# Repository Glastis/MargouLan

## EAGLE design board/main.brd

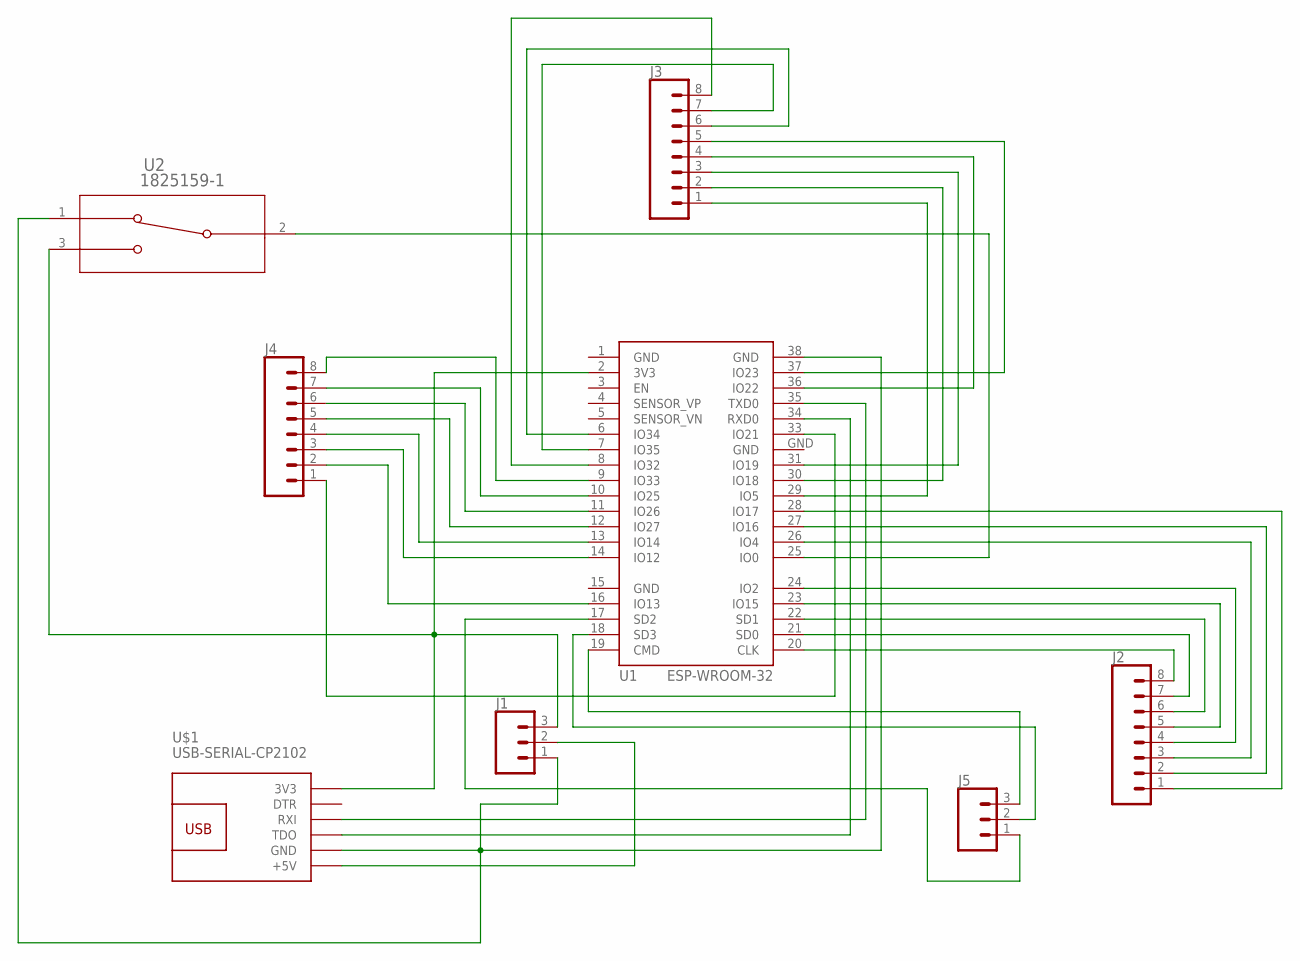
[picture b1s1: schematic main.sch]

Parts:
J1, J5: CONN_03; 1X03
J2, J3, J4: CONN_08"; 1X08
U1: ESP-WROOM-32
U2: 1825159-1; SW3-SLIDE-2POL_P98
U$1: USB-SERIAL-CP2102

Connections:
GND: U1.1 (GND), U1.15 (GND), U1.GND
unnamed: J1.3, U1.2 (3V3), U2.3 (2), U$1.1 (3V3)
unnamed: J1.1, U1.38 (GND), U2.1, U$1.5 (GND)
unnamed: U1.35 (TXD0), U$1.3 (RXI)
unnamed: U1.34 (RXD0), U$1.4 (TDO)
unnamed: U1.25 (IO0), U2.2 (3)
unnamed: J1.2, U$1.6 (+5V)
unnamed: J2.8, U1.20 (CLK)
unnamed: J2.7, U1.21 (SD0)
unnamed: J2.6, U1.22 (SD1)
unnamed: J2.5, U1.23 (IO15)
unnamed: J2.4, U1.24 (IO2)
unnamed: J2.3, U1.26 (IO4)
unnamed: J2.2, U1.27 (IO16)
unnamed: J2.1, U1.28 (IO17)
unnamed: J3.1, U1.29 (IO5)
unnamed: J3.2, U1.30 (IO18)
unnamed: J3.3, U1.31 (IO19)
unnamed: J3.4, U1.36 (IO22)
unnamed: J3.5, U1.37 (IO23)
unnamed: J3.6, U1.6 (IO34)
unnamed: J3.7, U1.7 (IO35)
unnamed: J3.8, U1.8 (IO32)
unnamed: J4.8, U1.9 (IO33)
unnamed: J4.7, U1.10 (IO25)
unnamed: J4.6, U1.11 (IO26)
unnamed: J4.5, U1.12 (IO27)
unnamed: J4.4, U1.13 (IO14)
unnamed: J4.3, U1.14 (IO12)
unnamed: J4.2, U1.16 (IO13)
unnamed: J4.1, U1.33 (IO21)
unnamed: J5.3, U1.19 (CMD)
unnamed: J5.2, U1.18 (SD3)
unnamed: J5.1, U1.17 (SD2)

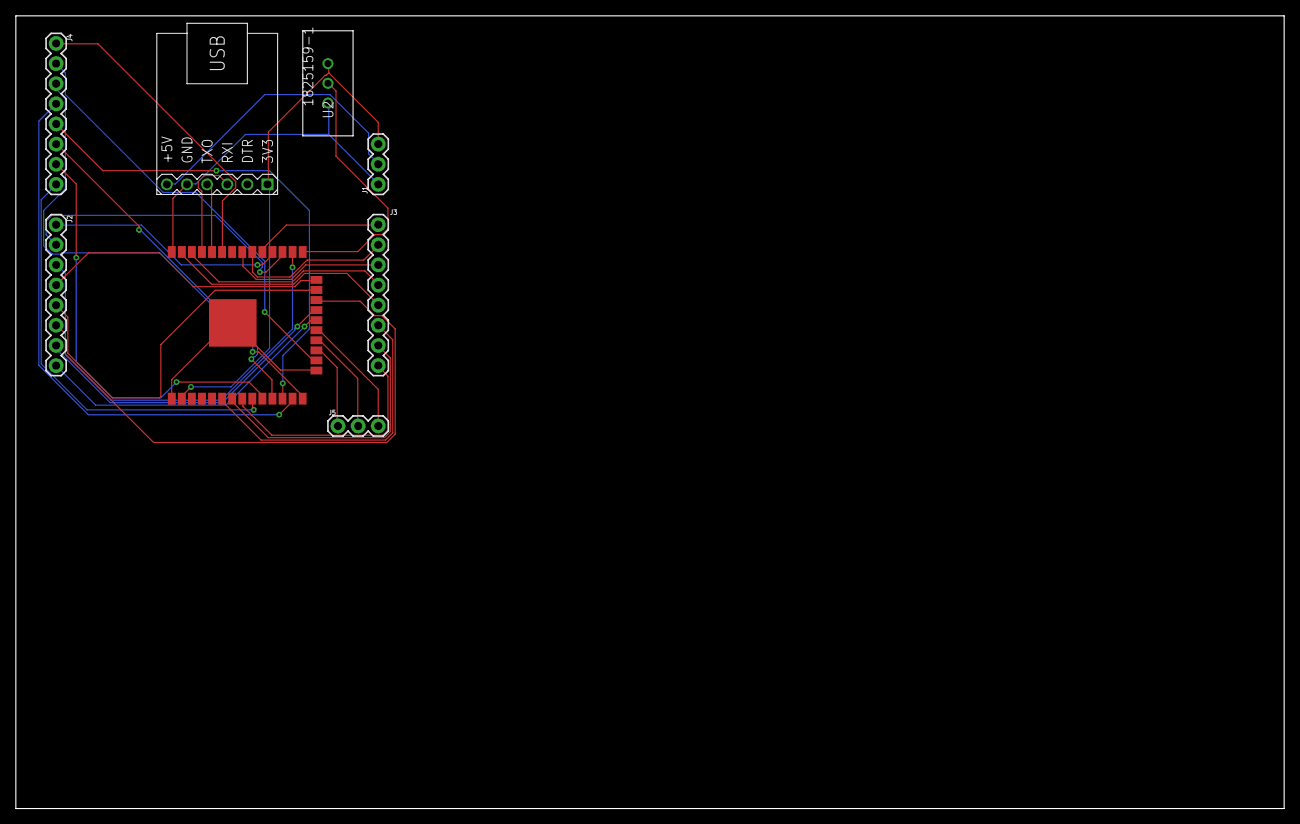
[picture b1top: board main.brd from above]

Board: 2 copper layers, 160.0 x 100.0 mm, 8 parts (0 on the bottom side), 34 nets.

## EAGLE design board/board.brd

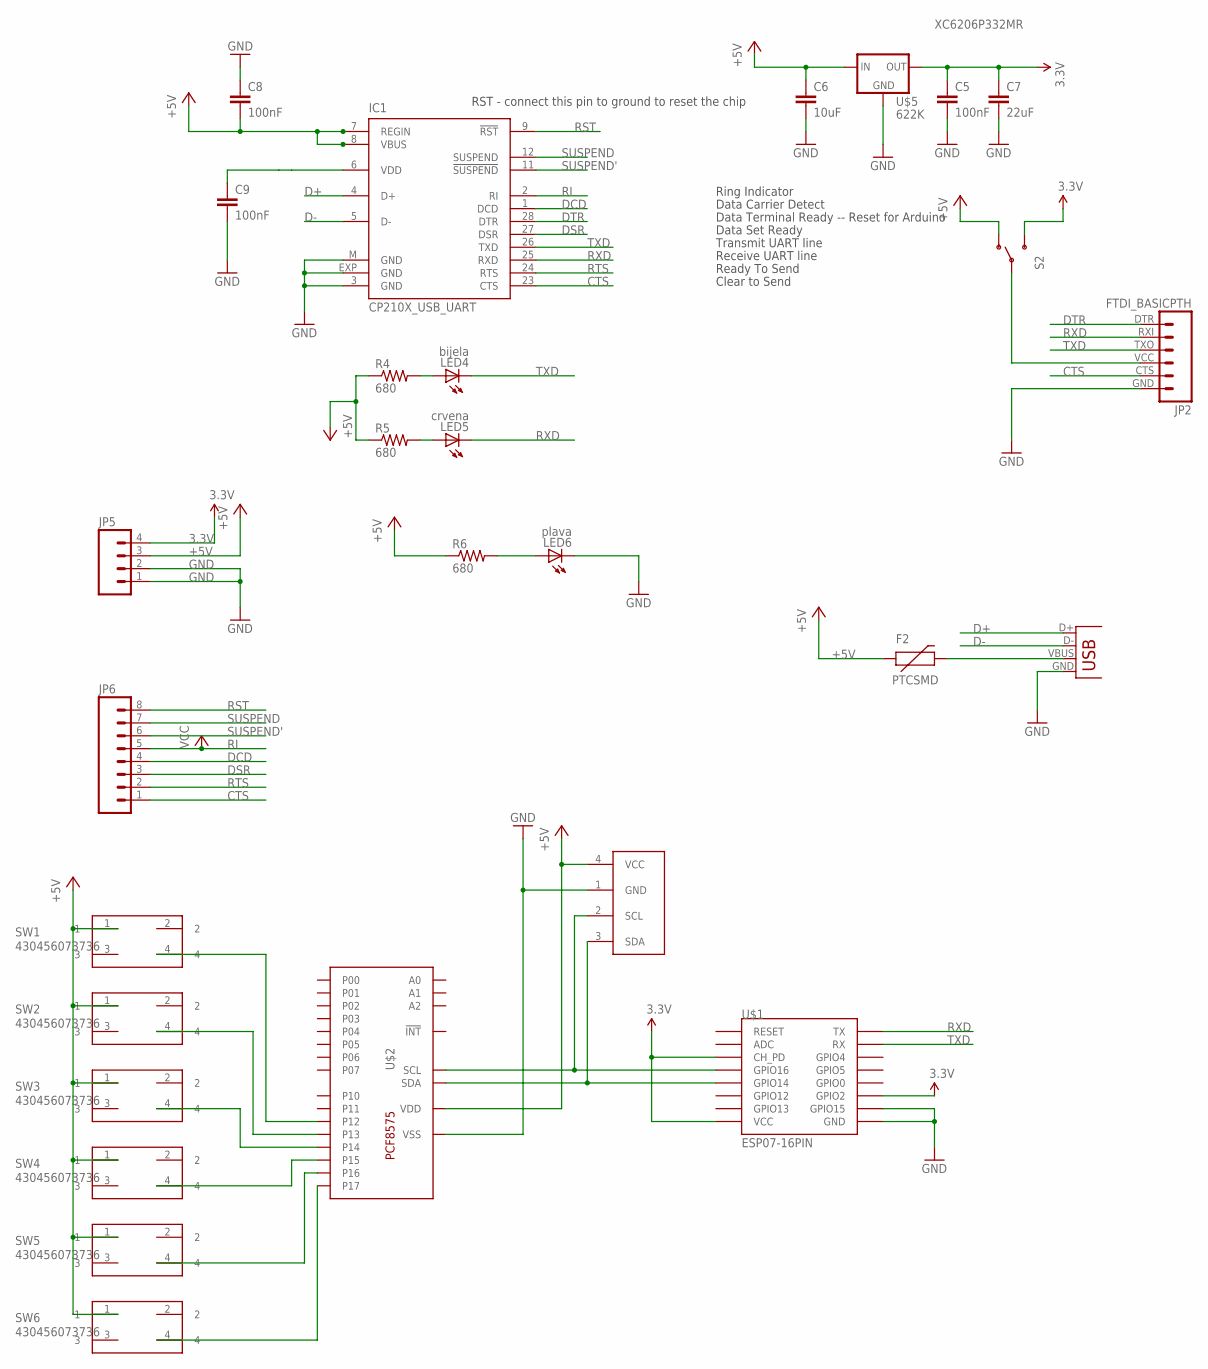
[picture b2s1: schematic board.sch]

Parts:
C5, C8, C9: 100nF; 0603-CAP
C6: 10uF; C3216
C7: 22uF; C3216
F2: PTCSMD; PTC-1206
IC1: CP210X_USB_UART; MLP28
JP2: FTDI_BASICPTH; FTDI_BASIC
JP5: M04PTH; 1X04
JP6: M081X08; 1X08
LED4: bijela; CHIP-LED0805
LED5: crvena; CHIP-LED0805
LED6: plava; CHIP-LED0805
R4, R5, R6: 680; 0603-RES
S2: SWITCH-SPST-SMD-A
SW1, SW2, SW3, SW4, SW5, SW6: 430456073736
U$1: ESP07-16PIN
U$2: PCF8575C; SOP24
U$3: I2C_OLED; I2C_OLED_PACKAGE
U$5: 622K; 662K
X2: USB-MICROB

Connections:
3.3V: C5.1, C7.1, JP5.4, S2.3 (S), U$1.CH_PD, U$1.GPIO2, U$1.VCC, U$5.OUT
+5V: C6.1, C8.2, F2.1, IC1.7 (REGIN), IC1.8 (VBUS), JP5.3, R4.1, R5.1, R6.1, S2.1 (O), SW1.1, SW2.1, SW3.1, SW4.1, SW5.1, SW6.1, U$2.P$24 (VDD), U$3.4 (VCC), U$5.IN
CTS: IC1.23 (CTS), JP2.CTS (5), JP6.1
D+: IC1.4 (D+), X2.D+
D-: IC1.5 (D-), X2.D-
DCD: IC1.1 (DCD), JP6.4
DSR: IC1.27 (DSR), JP6.3
DTR: IC1.28 (DTR), JP2.DTR (1)
GND: C5.2, C6.2, C7.2, C8.1, C9.2, IC1.3 (GND), IC1.EXP (GND), IC1.M (GND), JP2.GND (6), JP5.1, JP5.2, LED6.C, U$1.GND, U$1.GPIO15, U$2.P$12 (VSS), U$3.1 (GND), U$5.GND, X2.GND
unnamed: U$1.GPIO14, U$2.P$23 (SDA), U$3.3 (SDA)
unnamed: U$1.GPIO16, U$2.P$22 (SCL), U$3.2 (SCL)
unnamed: SW6.4, U$2.P$20 (P17)
unnamed: SW5.4, U$2.P$19 (P16)
unnamed: LED4.A, R4.2
unnamed: LED5.A, R5.2
unnamed: LED6.A, R6.2
unnamed: C9.1, IC1.6 (VDD)
unnamed: SW4.4, U$2.P$18 (P15)
unnamed: SW3.4, U$2.P$17 (P14)
unnamed: SW2.4, U$2.P$16 (P13)
unnamed: SW1.4, U$2.P$15 (P12)
RI: IC1.2 (RI), JP6.5
RST: IC1.9 (!RST), JP6.8
RTS: IC1.24 (RTS), JP6.2
RXD: IC1.25 (RXD), JP2.RXI (2), LED5.C, U$1.TX
SUSPEND: IC1.12 (SUSPEND), JP6.7
SUSPEND': IC1.11 (!SUSPEND), JP6.6
TXD: IC1.26 (TXD), JP2.TXO (3), LED4.C, U$1.RX
VBUS1: F2.2, X2.VBUS
VCC1: JP2.VCC (4), S2.2

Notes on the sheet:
RST - connect this pin to ground to reset the chip
Clear to Send
Data Terminal Ready -- Reset for Arduino
Data Set Ready
Transmit UART line
Receive UART line
Data Carrier Detect
Ring Indicator
Ready To Send
XC6206P332MR

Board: 2 copper layers, 28 parts (0 on the bottom side), 30 nets, no tracks yet.

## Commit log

2018-05-13 Screen, IO extender, buttons and wifi
2018-05-13 added gitignore file
2018-05-13 renamed margoulua_pas_lua to MargouLan
2018-05-13 Added menu
2018-05-15 Added eagle shematic
2020-04-08 updated board

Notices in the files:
parts and their libraries:
SparkFun: Licensing: CC v3.0 Share-Alike You are welcome to use this library for commercial purposes.
SparkFun-DigitalIC: Licensing: Creative Commons ShareAlike 4.0 International - https://creativecommons.org/licenses/by-sa/4.0
Wurth_Elektronik_Electromechanic_Switchs: Copyright: Würth Elektronik
